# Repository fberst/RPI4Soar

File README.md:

# RPI4Soar

RPI4Soar is a gliding computer based on the Raspbery Pi4B running XCsoar (https://www.xcsoar.org/)

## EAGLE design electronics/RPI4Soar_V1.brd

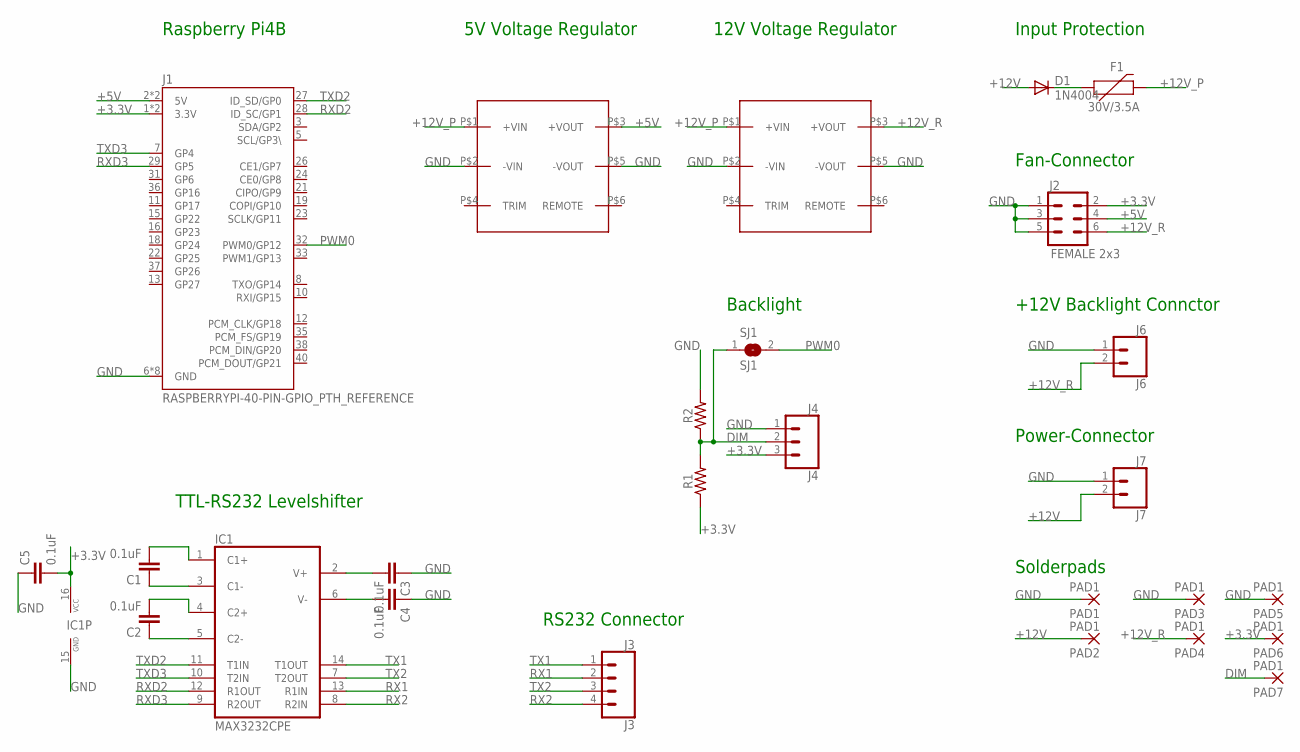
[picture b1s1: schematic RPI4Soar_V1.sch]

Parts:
C1, C2, C3, C4, C5: 0.1uF; CAP-PTH-SMALL-KIT
D1: 1N4004; DO41-10
F1: 30V/3.5A; PTH
IC1: MAX3232CPE; DIL16
J1: RASPBERRYPI-40-PIN-GPIO_PTH_REFERENCE; RASPBERRY_PI_HAT_40_PIN_PTH_WITH_REFERNCE
J2: FEMALE 2x3; 2X3
J3: J3; 1X04
J4: J4; 1X03
J6: J6; 1X02
J7: J7; 1X02
PAD1, PAD2, PAD3, PAD4, PAD5, PAD6, PAD7: PAD1; SMD2,54-5,08
R1, R2: AXIAL-0.3
SJ1: SJ1; SJ
U$1: TRACO_THN15WI +5V; TRACO_THN15WI
U$2: TRACO_THN15WI +12V; TRACO_THN15WI

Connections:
+3.3V: C5.2, IC1.16 (VCC), J1.1 (3.3V), J1.17 (3.3V), J2.2, J4.3, PAD6.1, R1.P$1 (1)
+5V: J1.2 (5V), J1.4 (5V), J2.4, U$1.P$3 (+VOUT)
+12V: D1.A, J7.2, PAD2.1
+12V_P: F1.P$2 (2), U$1.P$1 (+VIN), U$2.P$1 (+VIN)
+12V_R: J2.6, J6.2, PAD4.1, U$2.P$3 (+VOUT)
DIM: J4.2, PAD7.1, R1.P$2 (2), R2.P$1 (1), SJ1.1
GND: C3.1, C4.1, C5.1, IC1.15 (GND), J1.6 (GND), J1.9 (GND), J1.14 (GND), J1.20 (GND), J1.25 (GND), J1.30 (GND), J1.34 (GND), J1.39 (GND), J2.1, J2.3, J2.5, J4.1, J6.1, J7.1, PAD1.1, PAD3.1, PAD5.1, R2.P$2 (2), U$1.P$2 (-VIN), U$1.P$5 (-VOUT), U$2.P$2 (-VIN), U$2.P$5 (-VOUT)
unnamed: D1.C, F1.P$1 (1)
unnamed: C2.1, IC1.5 (C2-)
unnamed: C2.2, IC1.4 (C2+)
unnamed: C1.1, IC1.3 (C1-)
unnamed: C1.2, IC1.1 (C1+)
unnamed: C3.2, IC1.2 (V+)
unnamed: C4.2, IC1.6 (V-)
PWM0: J1.32 (PWM0/GP12), SJ1.2
RX1: IC1.13 (R1IN), J3.2
RX2: IC1.8 (R2IN), J3.4
RXD2: IC1.12 (R1OUT), J1.28 (ID_SC/GP1)
RXD3: IC1.9 (R2OUT), J1.29 (GP5)
TX1: IC1.14 (T1OUT), J3.1
TX2: IC1.7 (T2OUT), J3.3
TXD2: IC1.11 (T1IN), J1.27 (ID_SD/GP0)
TXD3: IC1.10 (T2IN), J1.7 (GP4)

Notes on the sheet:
Raspberry Pi4B
5V Voltage Regulator
12V Voltage Regulator
Input Protection
Fan-Connector
+12V Backlight Connctor
Power-Connector
Backlight
TTL-RS232 Levelshifter
RS232 Connector
Solderpads

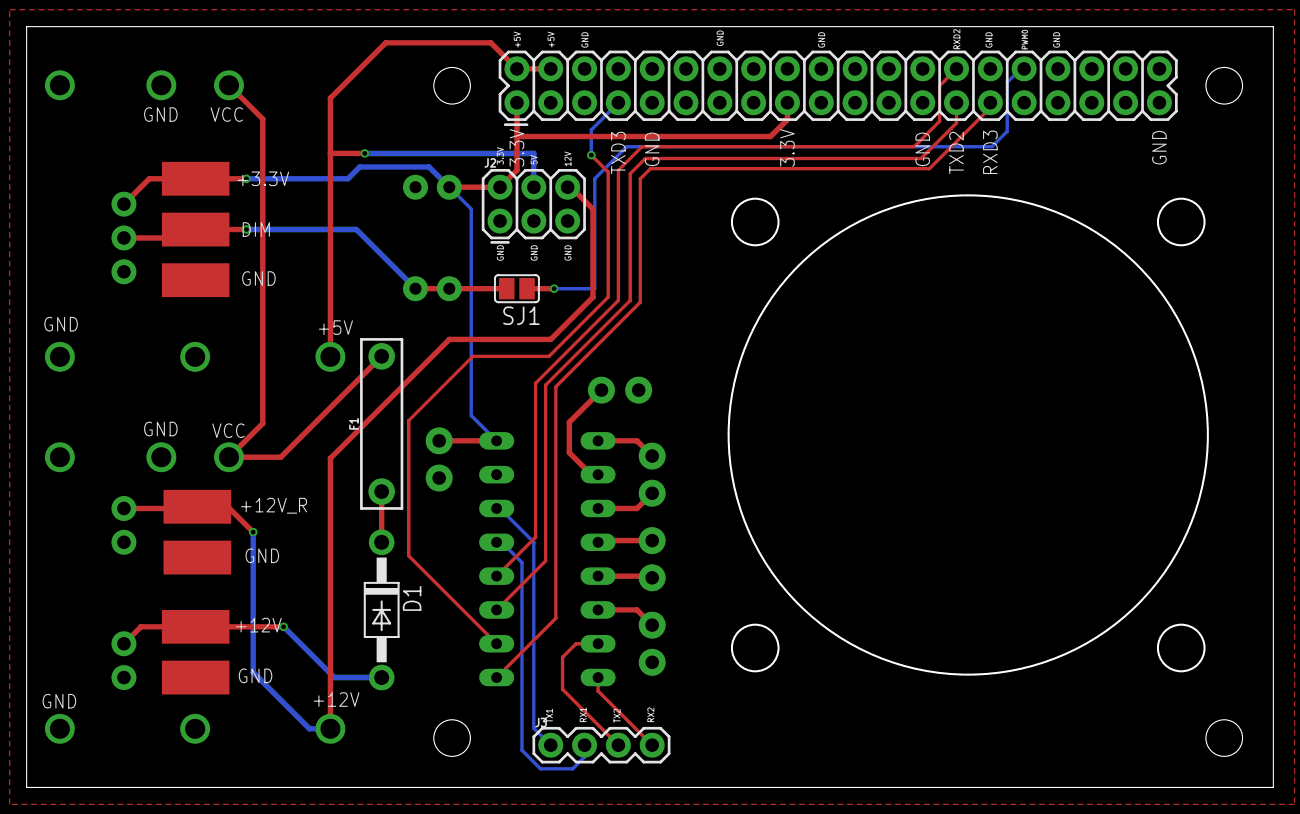
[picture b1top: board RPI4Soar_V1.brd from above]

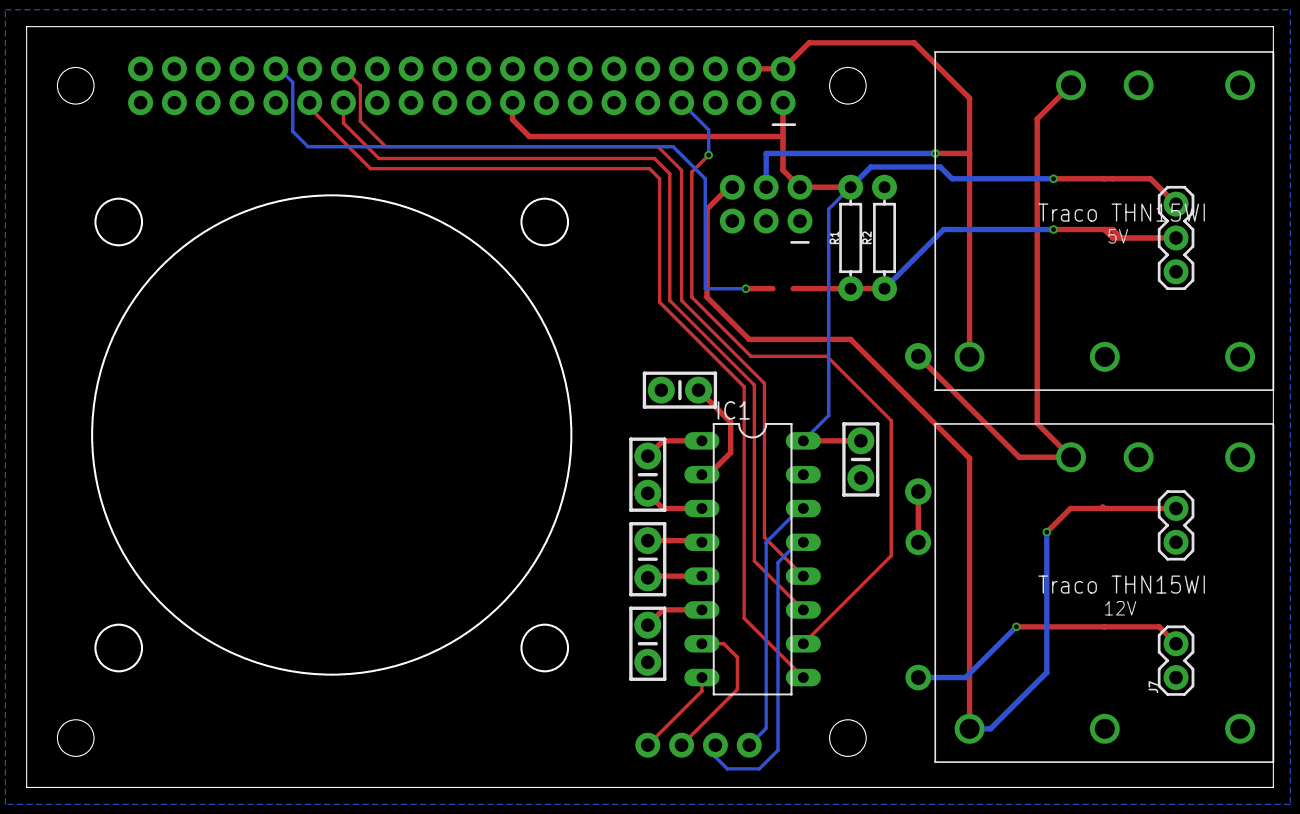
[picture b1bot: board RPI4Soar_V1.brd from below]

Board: 2 copper layers, 93.5 x 57.0 mm, 26 parts (13 on the bottom side), 23 nets.

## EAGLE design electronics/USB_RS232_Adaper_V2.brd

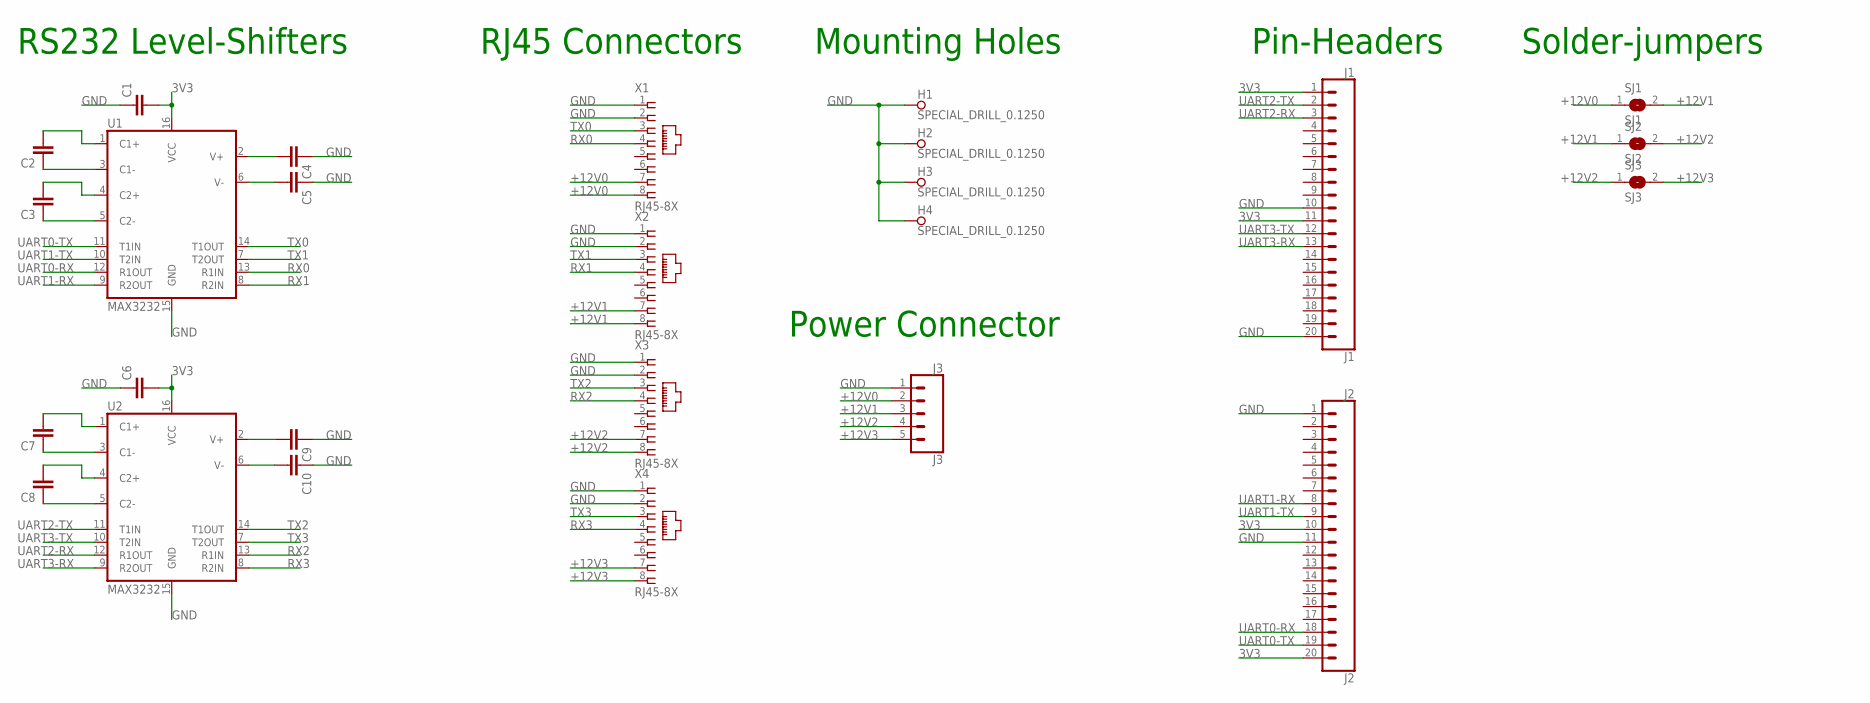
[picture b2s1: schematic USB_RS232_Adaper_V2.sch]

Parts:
C1, C2, C3, C4, C5, C6, C7, C8, C9, C10: 0.1uF; 0805
H1, H2, H3, H4: SPECIAL_DRILL_0.1250; PAD_0.1250
J1: J1; 1X20
J2: J2; 1X20
J3: J3; 1X05
SJ1: SJ1; SJ
SJ2: SJ2; SJ
SJ3: SJ3; SJ
U1, U2: MAX3232; SO16
X1, X2, X3, X4: RJ45-8X; RJ45-NO-SHIELD

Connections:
3V3: C1.2, C6.2, J1.1, J1.11, J2.10, J2.20, U1.16 (VCC), U2.16 (VCC)
+12V0: J3.2, SJ1.1, X1.7, X1.8
+12V1: J3.3, SJ1.2, SJ2.1, X2.7, X2.8
+12V2: J3.4, SJ2.2, SJ3.1, X3.7, X3.8
+12V3: J3.5, SJ3.2, X4.7, X4.8
GND: C1.1, C4.1, C5.1, C6.1, C9.1, C10.1, H1.1, H2.1, H3.1, H4.1, J1.10, J1.20, J2.1, J2.11, J3.1, U1.15 (GND), U2.15 (GND), X1.1, X1.2, X2.1, X2.2, X3.1, X3.2, X4.1, X4.2
unnamed: C2.1, U1.3 (C1-)
unnamed: C2.2, U1.1 (C1+)
unnamed: C3.1, U1.5 (C2-)
unnamed: C3.2, U1.4 (C2+)
unnamed: C4.2, U1.2 (V+)
unnamed: C5.2, U1.6 (V-)
unnamed: C9.2, U2.2 (V+)
unnamed: C10.2, U2.6 (V-)
unnamed: C7.1, U2.3 (C1-)
unnamed: C8.1, U2.5 (C2-)
unnamed: C8.2, U2.4 (C2+)
unnamed: C7.2, U2.1 (C1+)
RX0: U1.13 (R1IN), X1.4
RX1: U1.8 (R2IN), X2.4
RX2: U2.13 (R1IN), X3.4
RX3: U2.8 (R2IN), X4.4
TX0: U1.14 (T1OUT), X1.3
TX1: U1.7 (T2OUT), X2.3
TX2: U2.14 (T1OUT), X3.3
TX3: U2.7 (T2OUT), X4.3
UART0-RX: J2.18, U1.12 (R1OUT)
UART0-TX: J2.19, U1.11 (T1IN)
UART1-RX: J2.8, U1.9 (R2OUT)
UART1-TX: J2.9, U1.10 (T2IN)
UART2-RX: J1.3, U2.12 (R1OUT)
UART2-TX: J1.2, U2.11 (T1IN)
UART3-RX: J1.13, U2.9 (R2OUT)
UART3-TX: J1.12, U2.10 (T2IN)

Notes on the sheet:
RS232 Level-Shifters
RJ45 Connectors
Mounting Holes
Power Connector
Pin-Headers
Solder-jumpers

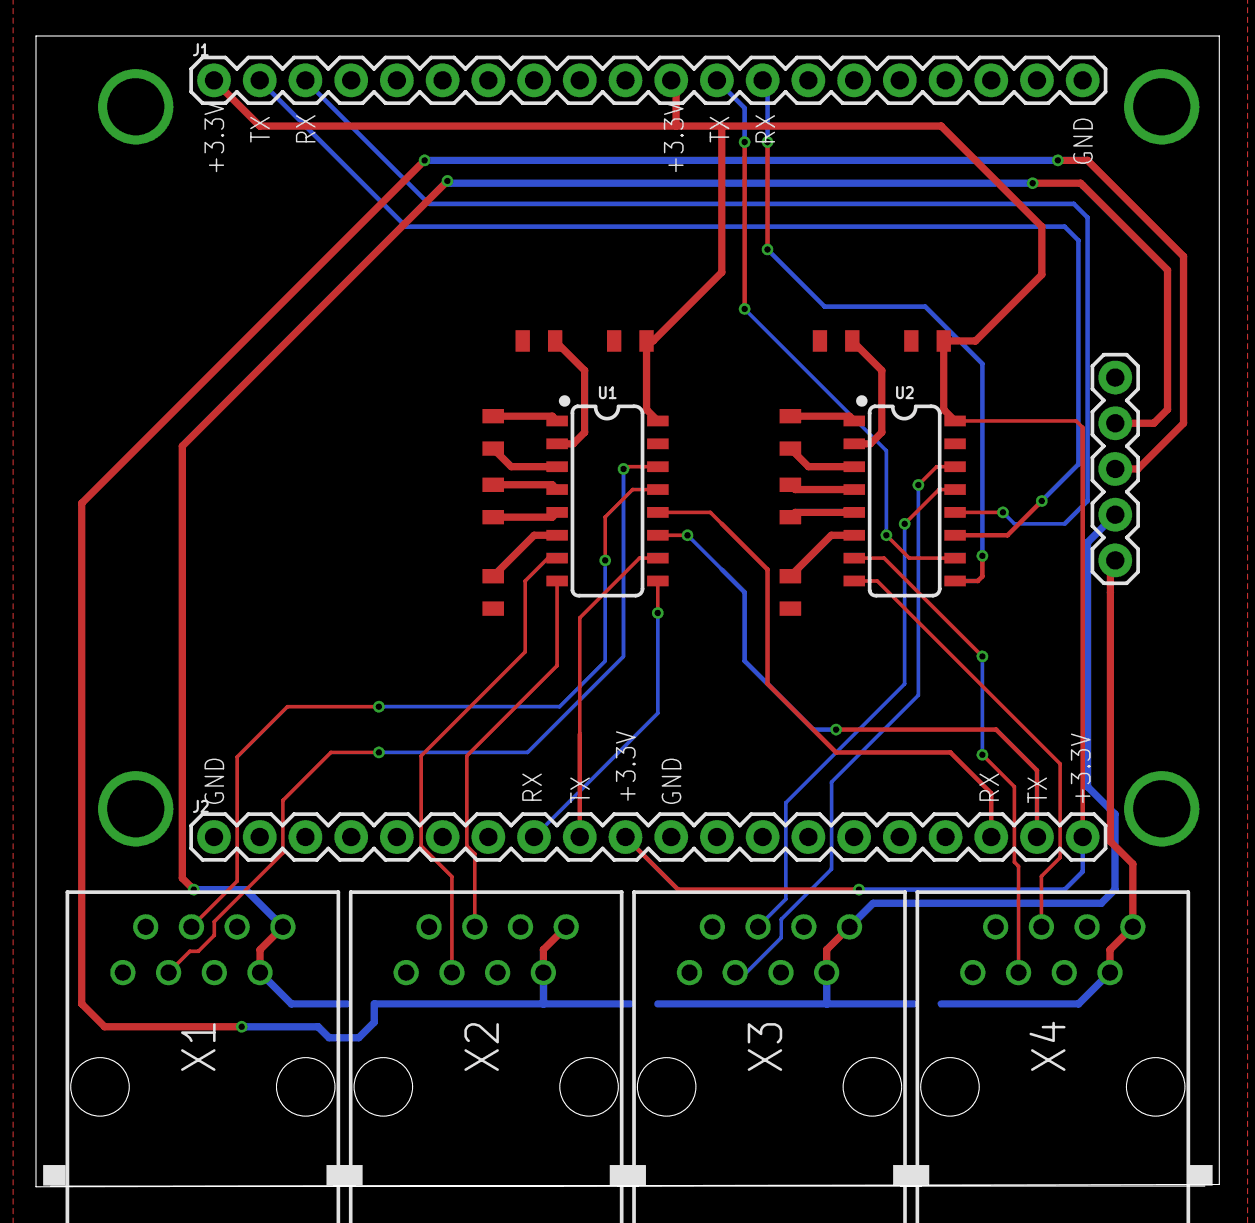
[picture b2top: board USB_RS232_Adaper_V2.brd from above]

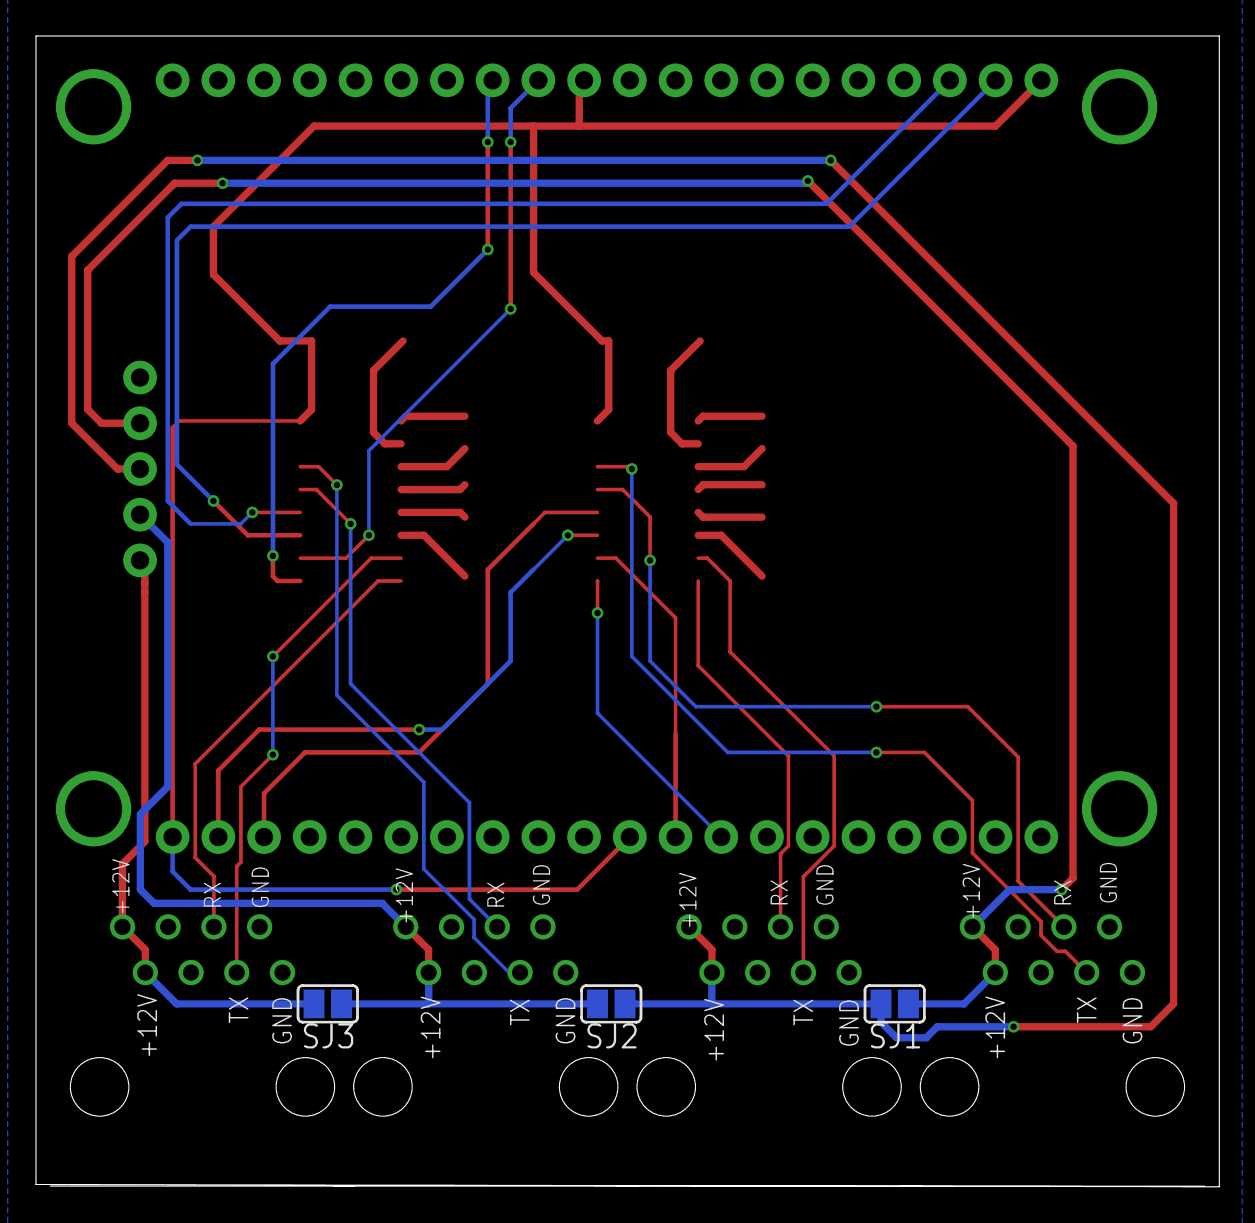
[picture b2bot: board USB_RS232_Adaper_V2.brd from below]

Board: 2 copper layers, 65.7 x 63.9 mm, 26 parts (3 on the bottom side), 34 nets.

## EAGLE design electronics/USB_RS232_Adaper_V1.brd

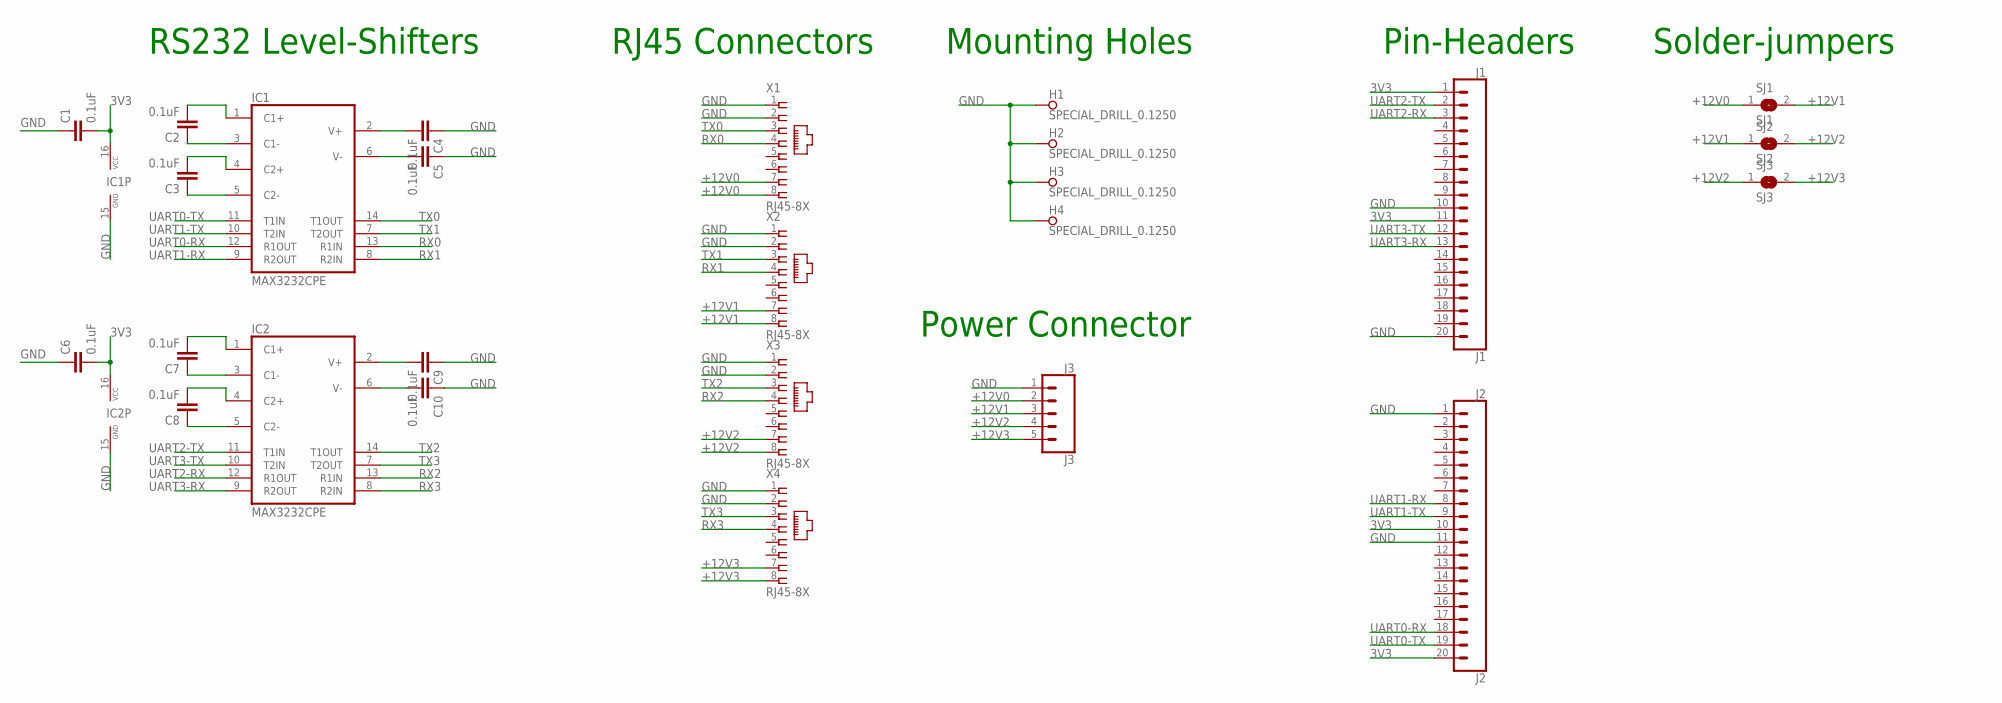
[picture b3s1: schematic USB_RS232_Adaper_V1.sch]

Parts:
C1, C2, C3, C4, C5, C6, C7, C8, C9, C10: 0.1uF; CAP-PTH-SMALL-KIT
H1, H2, H3, H4: SPECIAL_DRILL_0.1250; PAD_0.1250
IC1, IC2: MAX3232CPE; DIL16
J1: J1; 1X20
J2: J2; 1X20
J3: J3; 1X05
SJ1: SJ1; SJ
SJ2: SJ2; SJ
SJ3: SJ3; SJ
X1, X2, X3, X4: RJ45-8X; RJ45-NO-SHIELD

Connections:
3V3: C1.2, C6.2, IC1.16 (VCC), IC2.16 (VCC), J1.1, J1.11, J2.10, J2.20
+12V0: J3.2, SJ1.1, X1.7, X1.8
+12V1: J3.3, SJ1.2, SJ2.1, X2.7, X2.8
+12V2: J3.4, SJ2.2, SJ3.1, X3.7, X3.8
+12V3: J3.5, SJ3.2, X4.7, X4.8
GND: C1.1, C4.1, C5.1, C6.1, C9.1, C10.1, H1.1, H2.1, H3.1, H4.1, IC1.15 (GND), IC2.15 (GND), J1.10, J1.20, J2.1, J2.11, J3.1, X1.1, X1.2, X2.1, X2.2, X3.1, X3.2, X4.1, X4.2
unnamed: C4.2, IC1.2 (V+)
unnamed: C5.2, IC1.6 (V-)
unnamed: C2.1, IC1.3 (C1-)
unnamed: C2.2, IC1.1 (C1+)
unnamed: C3.1, IC1.5 (C2-)
unnamed: C3.2, IC1.4 (C2+)
unnamed: C9.2, IC2.2 (V+)
unnamed: C10.2, IC2.6 (V-)
unnamed: C7.1, IC2.3 (C1-)
unnamed: C7.2, IC2.1 (C1+)
unnamed: C8.1, IC2.5 (C2-)
unnamed: C8.2, IC2.4 (C2+)
RX0: IC1.13 (R1IN), X1.4
RX1: IC1.8 (R2IN), X2.4
RX2: IC2.13 (R1IN), X3.4
RX3: IC2.8 (R2IN), X4.4
TX0: IC1.14 (T1OUT), X1.3
TX1: IC1.7 (T2OUT), X2.3
TX2: IC2.14 (T1OUT), X3.3
TX3: IC2.7 (T2OUT), X4.3
UART0-RX: IC1.12 (R1OUT), J2.18
UART0-TX: IC1.11 (T1IN), J2.19
UART1-RX: IC1.9 (R2OUT), J2.8
UART1-TX: IC1.10 (T2IN), J2.9
UART2-RX: IC2.12 (R1OUT), J1.3
UART2-TX: IC2.11 (T1IN), J1.2
UART3-RX: IC2.9 (R2OUT), J1.13
UART3-TX: IC2.10 (T2IN), J1.12

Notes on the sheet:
RS232 Level-Shifters
RJ45 Connectors
Mounting Holes
Power Connector
Pin-Headers
Solder-jumpers

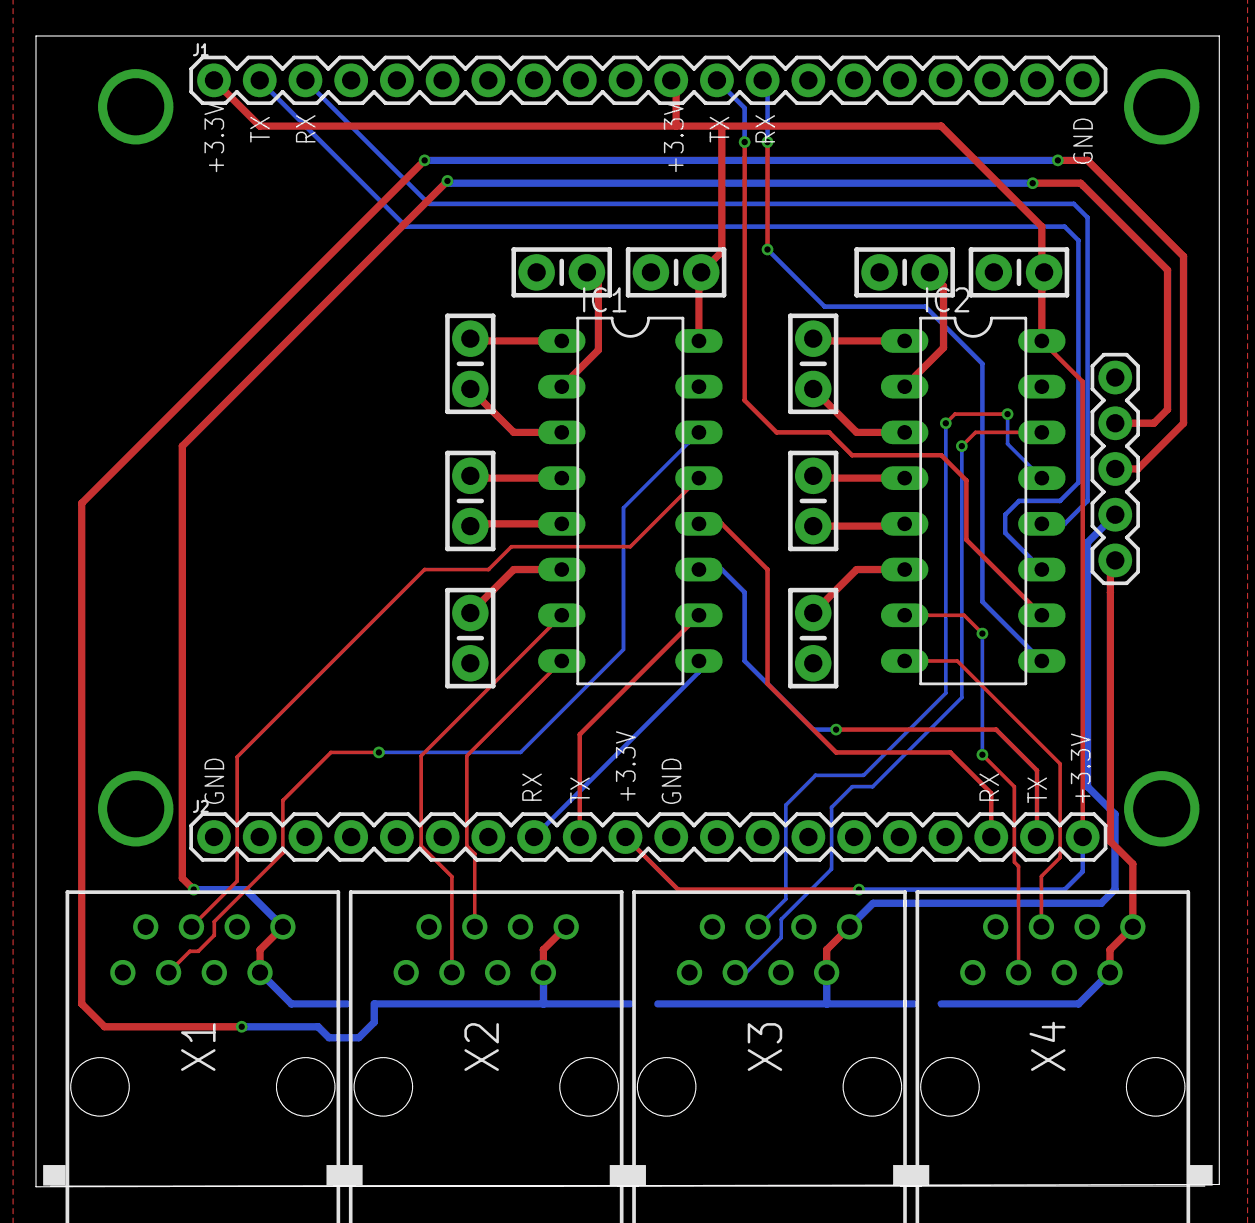
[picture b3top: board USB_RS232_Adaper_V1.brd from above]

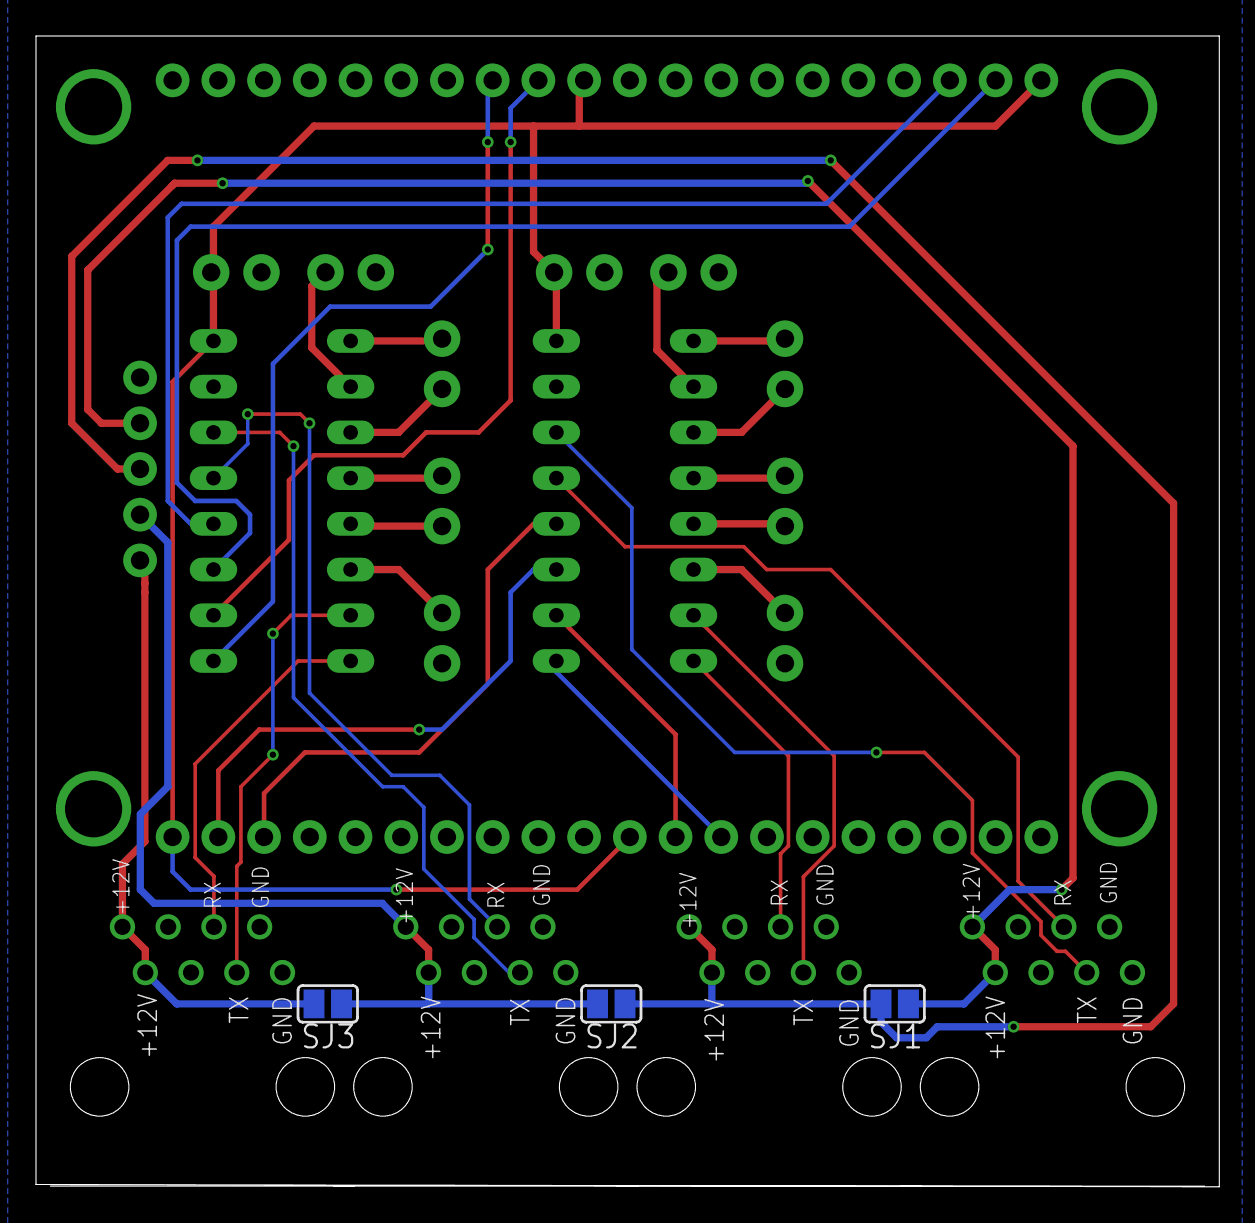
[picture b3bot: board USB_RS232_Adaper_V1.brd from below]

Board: 2 copper layers, 65.7 x 63.9 mm, 26 parts (3 on the bottom side), 34 nets.

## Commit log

2023-02-23 add RPI4Soar_V1 CAD files
2023-02-23 add USB_RS232_Adapter CAD files
2023-02-23 add RPI4Soar power supply pcb
2023-02-23 add USB_RS232_Adapter_V1 pcb
2023-02-23 add BOM_USB_RS232_Adapter
2023-02-24 add cc by-sa 4.0 license text
2023-02-24 change README.md and add picture
2023-02-25 CAD: add RPISoar_V2
2023-02-26 CAD: add template for panel cutout
2023-02-26 added USB_RS232_Adapter_V2
2023-02-26 pictures: add USB_RS232_Adapter_V1 pictures
2023-02-26 add RPI4Soar BOM
2025-08-31 BOM_USB_RS232_V1.ods: add missing parts
2025-08-31 BOM_USB_RS232_V2.ods: add missing parts

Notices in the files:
parts and their libraries:
SparkFun-Connectors: Licensing: Creative Commons ShareAlike 4.0 International - https://creativecommons.org/licenses/by-sa/4.0
